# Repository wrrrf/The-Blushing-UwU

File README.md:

# Keypad
Our project is a keypad for the rhythm game osu! that has leds that get brighter the faster you tap, these leds would be behind eyes or a blush or something so whatever we end up plastering on our keypad will have its eyes get brighter / blush harder when you tap faster. 
We made the project because we got bored over the summer and I also happen to want a keypad to play osu because my current keyboard is quite low quality.

In the end I decided to have maomao from apothecary diaries as my keypad and the eyes light up when u tap faster\
\
the pcb:
\

| Item No. | Quantity | Part No.                  | Desc                           | Link                                                                                                                                                                                                         | Price |                                                                                                                        |
|----------|----------|---------------------------|--------------------------------|--------------------------------------------------------------------------------------------------------------------------------------------------------------------------------------------------------------|-------|------------------------------------------------------------------------------------------------------------------------|
| 1        | 1        | case/case.step            | 3d print this                  |                                                                                                                                                                                                              | 20    |                                                                                                                        |
| 2        | 1        | case/face_plate.step      | 3d print this                  |                                                                                                                                                                                                              |       |                                                                                                                        |
| 3        | 1        | case/eye_white_left.step  | 3d print this                  | Amazon.com: 15 Bright Colors 1.75mm 3D Pen PLA Filament Refill, Each Color 10feet, Total 150 Feet 3D Pen/3D Printer PLA Sample Pack, Compatible with MYNT3D / SCRIB3D Printing Pen : Industrial & Scientific | $8    | a 1.75mm 3d pen refill should be enough to print all pieces (printed 1-2 layers high so light may still shine through) |
| 4        | 1        | case/eye_white_right.step | 3d print this                  |                                                                                                                                                                                                              |       |                                                                                                                        |
| 5        | 1        | case/star_left.step       | 3d print this                  |                                                                                                                                                                                                              |       |                                                                                                                        |
| 6        | 1        | case/star_right.step      | 3d print this                  |                                                                                                                                                                                                              |       |                                                                                                                        |
| 7        | 1        | case/iris_1.step          | 3d print this                  |                                                                                                                                                                                                              |       |                                                                                                                        |
| 8        | 1        | case/iris_2.step          | 3d print this                  |                                                                                                                                                                                                              |       |                                                                                                                        |
| 9        | 1        | case/iris_3.step          | 3d print this                  |                                                                                                                                                                                                              |       |                                                                                                                        |
| 10       | 1        | case/iris_4.step          | 3d print this                  |                                                                                                                                                                                                              |       |                                                                                                                        |
| 11       | 1        | case/iris_5.step          | 3d print this                  |                                                                                                                                                                                                              |       |                                                                                                                        |
| 12       | 1        | case/iris_6.step          | 3d print this                  |                                                                                                                                                                                                              |       |                                                                                                                        |
| 13       | 1        | case/iris_7.step          | 3d print this                  |                                                                                                                                                                                                              |       |                                                                                                                        |
| 14       | 1        | case/iris_8.step          | 3d print this                  |                                                                                                                                                                                                              |       |                                                                                                                        |
| 15       | 3        | Cherry MX reds            | switches                       |                                                                                                                                                                                                              | 1.2   |                                                                                                                        |
| 16       | 3        |                           | some sort of cherry mx keycaps |                                                                                                                                                                                                              | 1.2   |                                                                                                                        |
| 17       | 1        | XIAO RP 2040 DIM          | Primary chip                   | Seeed Studio XIAO RP2040, Mini Arduino Dev Board with RP2040 and MicroPython Support                                                                                                                         | $3.90 |                                                                                                                        |
| 18       | 3        |                           | diode of some sort             |                                                                                                                                                                                                              | 2     |                                                                                                                        |
| 19       | 2        | SK6812 Mini               | RGB LEDs                       |                                                                                                                                                                                                              | 3     |                                                                                                                        |
| 20       | 1        | ./pcb                     | PCB                            |                                                                                                                                                                                                              | $3    |                                                                                                                        |
|          |          |                           |                                |                                                                                                                                                                                                              | 42.3  |                                                                                                                        |

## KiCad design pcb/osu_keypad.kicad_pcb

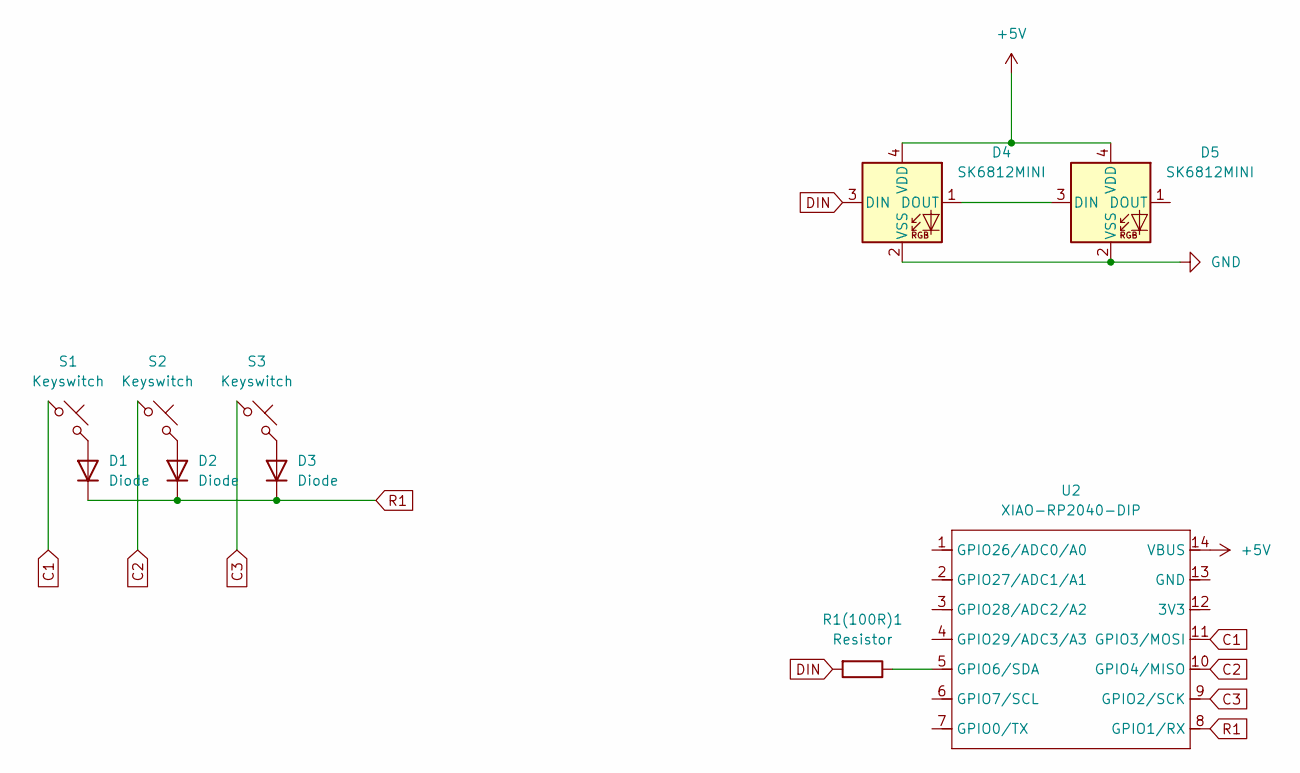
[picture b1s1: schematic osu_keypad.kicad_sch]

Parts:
D1, D2, D3: Diode; Diode_DO-35
D4, D5: SK6812MINI; LED_SK6812MINI_PLCC4_3.5x3.5mm_P1.75mm
R1(100R)1: Resistor; Resistor_0402
S1, S2, S3: Keyswitch; MX_PCB_1.00u
U2: XIAO-RP2040-DIP

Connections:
+5V: D4.4 (VDD), D5.4 (VDD), U2.14 (VBUS); also elsewhere on the board
C1: S1.1, U2.11 (GPIO3/MOSI); also elsewhere on the board
C2: S2.1, U2.10 (GPIO4/MISO); also elsewhere on the board
C3: S3.1, U2.9 (GPIO2/SCK); also elsewhere on the board
DIN: D4.3 (DIN), R1(100R)1.2
GND: D4.2 (VSS), D5.2 (VSS)
unnamed: D1.2 (A), S1.2
unnamed: D2.2 (A), S2.2
unnamed: D3.2 (A), S3.2
unnamed: D4.1 (DOUT), D5.3 (DIN)
unnamed 10: R1(100R)1.1, U2.5 (GPIO6/SDA); also elsewhere on the board
R1: D1.1 (K), D2.1 (K), D3.1 (K), U2.8 (GPIO1/RX); also elsewhere on the board

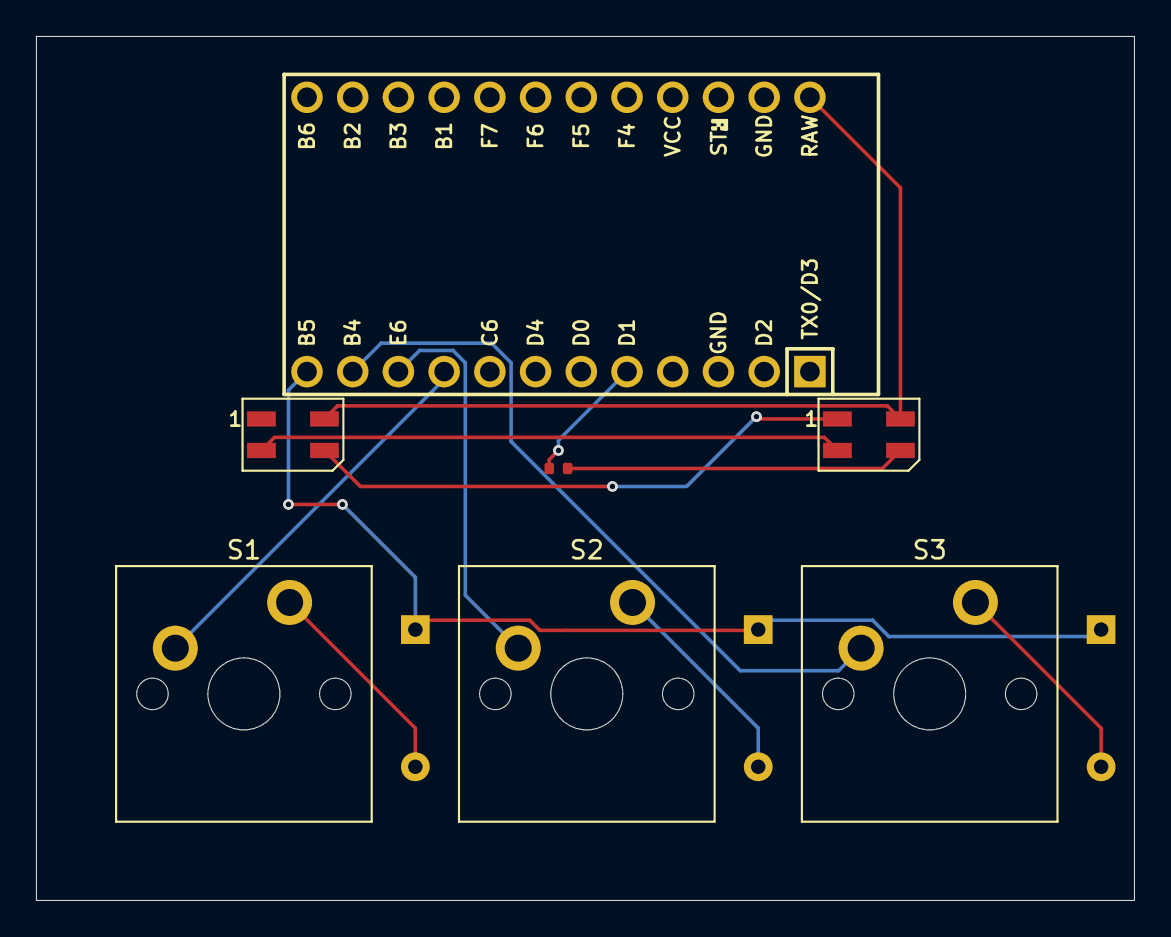
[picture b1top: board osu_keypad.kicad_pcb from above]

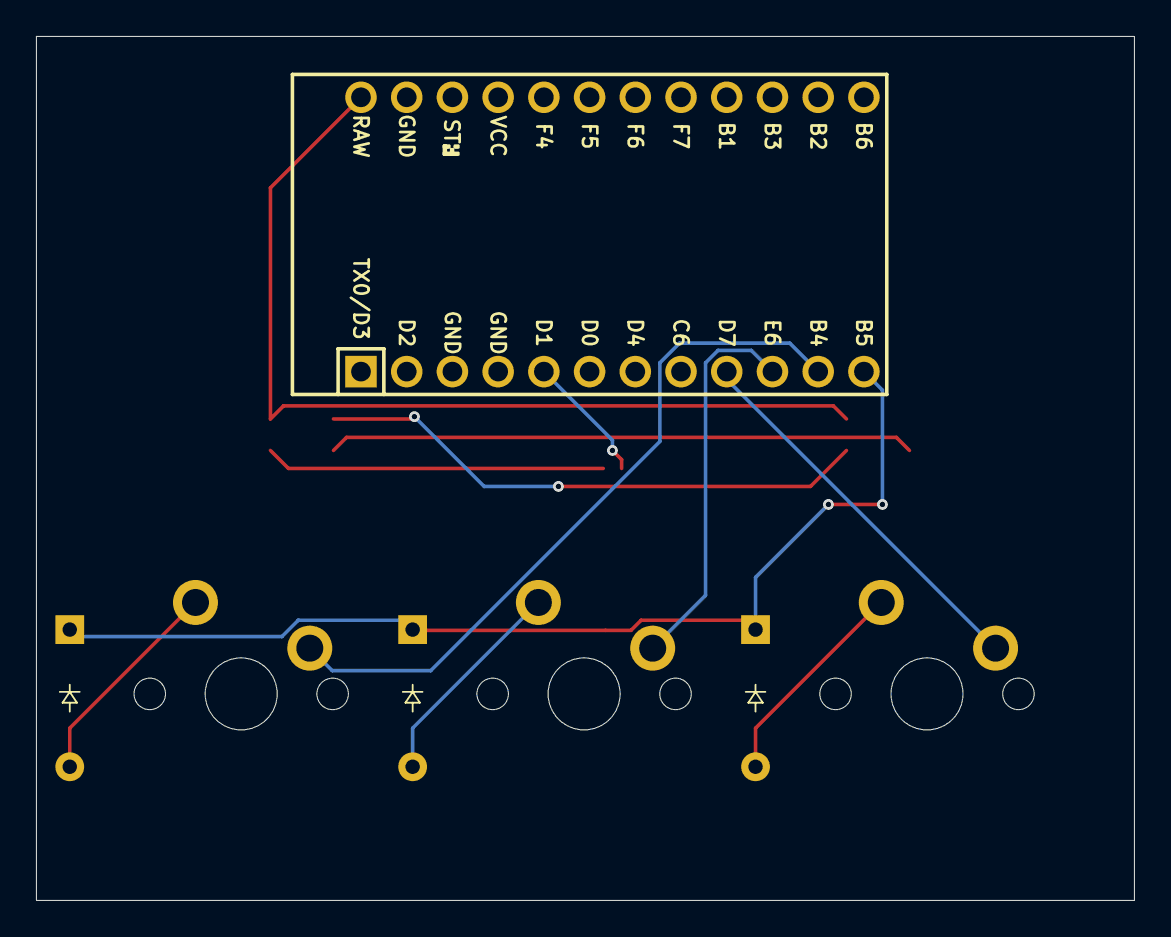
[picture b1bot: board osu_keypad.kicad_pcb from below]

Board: 2 copper layers, 61.0 x 48.0 mm, 10 parts (4 on the bottom side), 12 nets.

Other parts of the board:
U1: Arduino_Pro_Micro

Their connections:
+5V: U1.24 (RAW); also elsewhere on the board
C1: U1.9 (6/PD7); also elsewhere on the board
C2: U1.10 (7/PE6); also elsewhere on the board
C3: U1.11 (8/PB4); also elsewhere on the board
unnamed 10: U1.5 (2/PD1); also elsewhere on the board
R1: U1.12 (9/PB5); also elsewhere on the board

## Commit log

2025-06-03 Create placeholder
2025-06-03 Rename Screenshot 2025-06-03 120201.jpg to 6-02-2025
2025-06-03 Rename 6-02-2025 to 6-02-2025.jpg
2025-06-05 Rename 6-02-2025.jpg to 6-02-2025.jpg
2025-06-05 Rename Journal.md to Gallery/Journal.md
2025-06-05 Rename 6-02-2025.jpg to 6-02-25.jpg
2025-06-05 Rename 6-02-25.jpg to 06-02-25.jpg
2025-06-07 Rename 06-06-25.jpg to Gallery/06-06-25.jpg
2025-06-21 Update and rename bom - Sheet1.csv to Bill of Materials
2025-07-09 Add files via upload
    uploaded proper gerber files
